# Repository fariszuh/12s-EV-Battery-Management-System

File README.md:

# 12s Battery Management System Research Project

## Introduction
*This repo used to collaborative work on BMS project*
This project initiated by Anargya Third Generation Electric Manager Plan, Abyqa on 2021.
He suggested us (4th Electric Generation) to create our independent BMS. 
In the next year, 2022, We (Rafli as Electric Manager, Faris as Head of Low Voltage Subdiv., Lazu as Head of High Voltage Subdiv) proposed new design according to last Molina BMS.
The schematics design is located in /Single Board 12s directory. Note: use the latest version _v<number>.sch

## My Last Progress
Last progress was programming with Arduino UNO (Faris, Gagas). 
The code located inside /Code directory.

## Challenge
PCB had been assembly with the components, but the SPI communication to LTC's register still couldn't be read. 
This problem probably caused by thin route layer between component pin to LTC. You can re-route Eagle board file and print again.
Suggestion: use thicker path and more than 2 layer.

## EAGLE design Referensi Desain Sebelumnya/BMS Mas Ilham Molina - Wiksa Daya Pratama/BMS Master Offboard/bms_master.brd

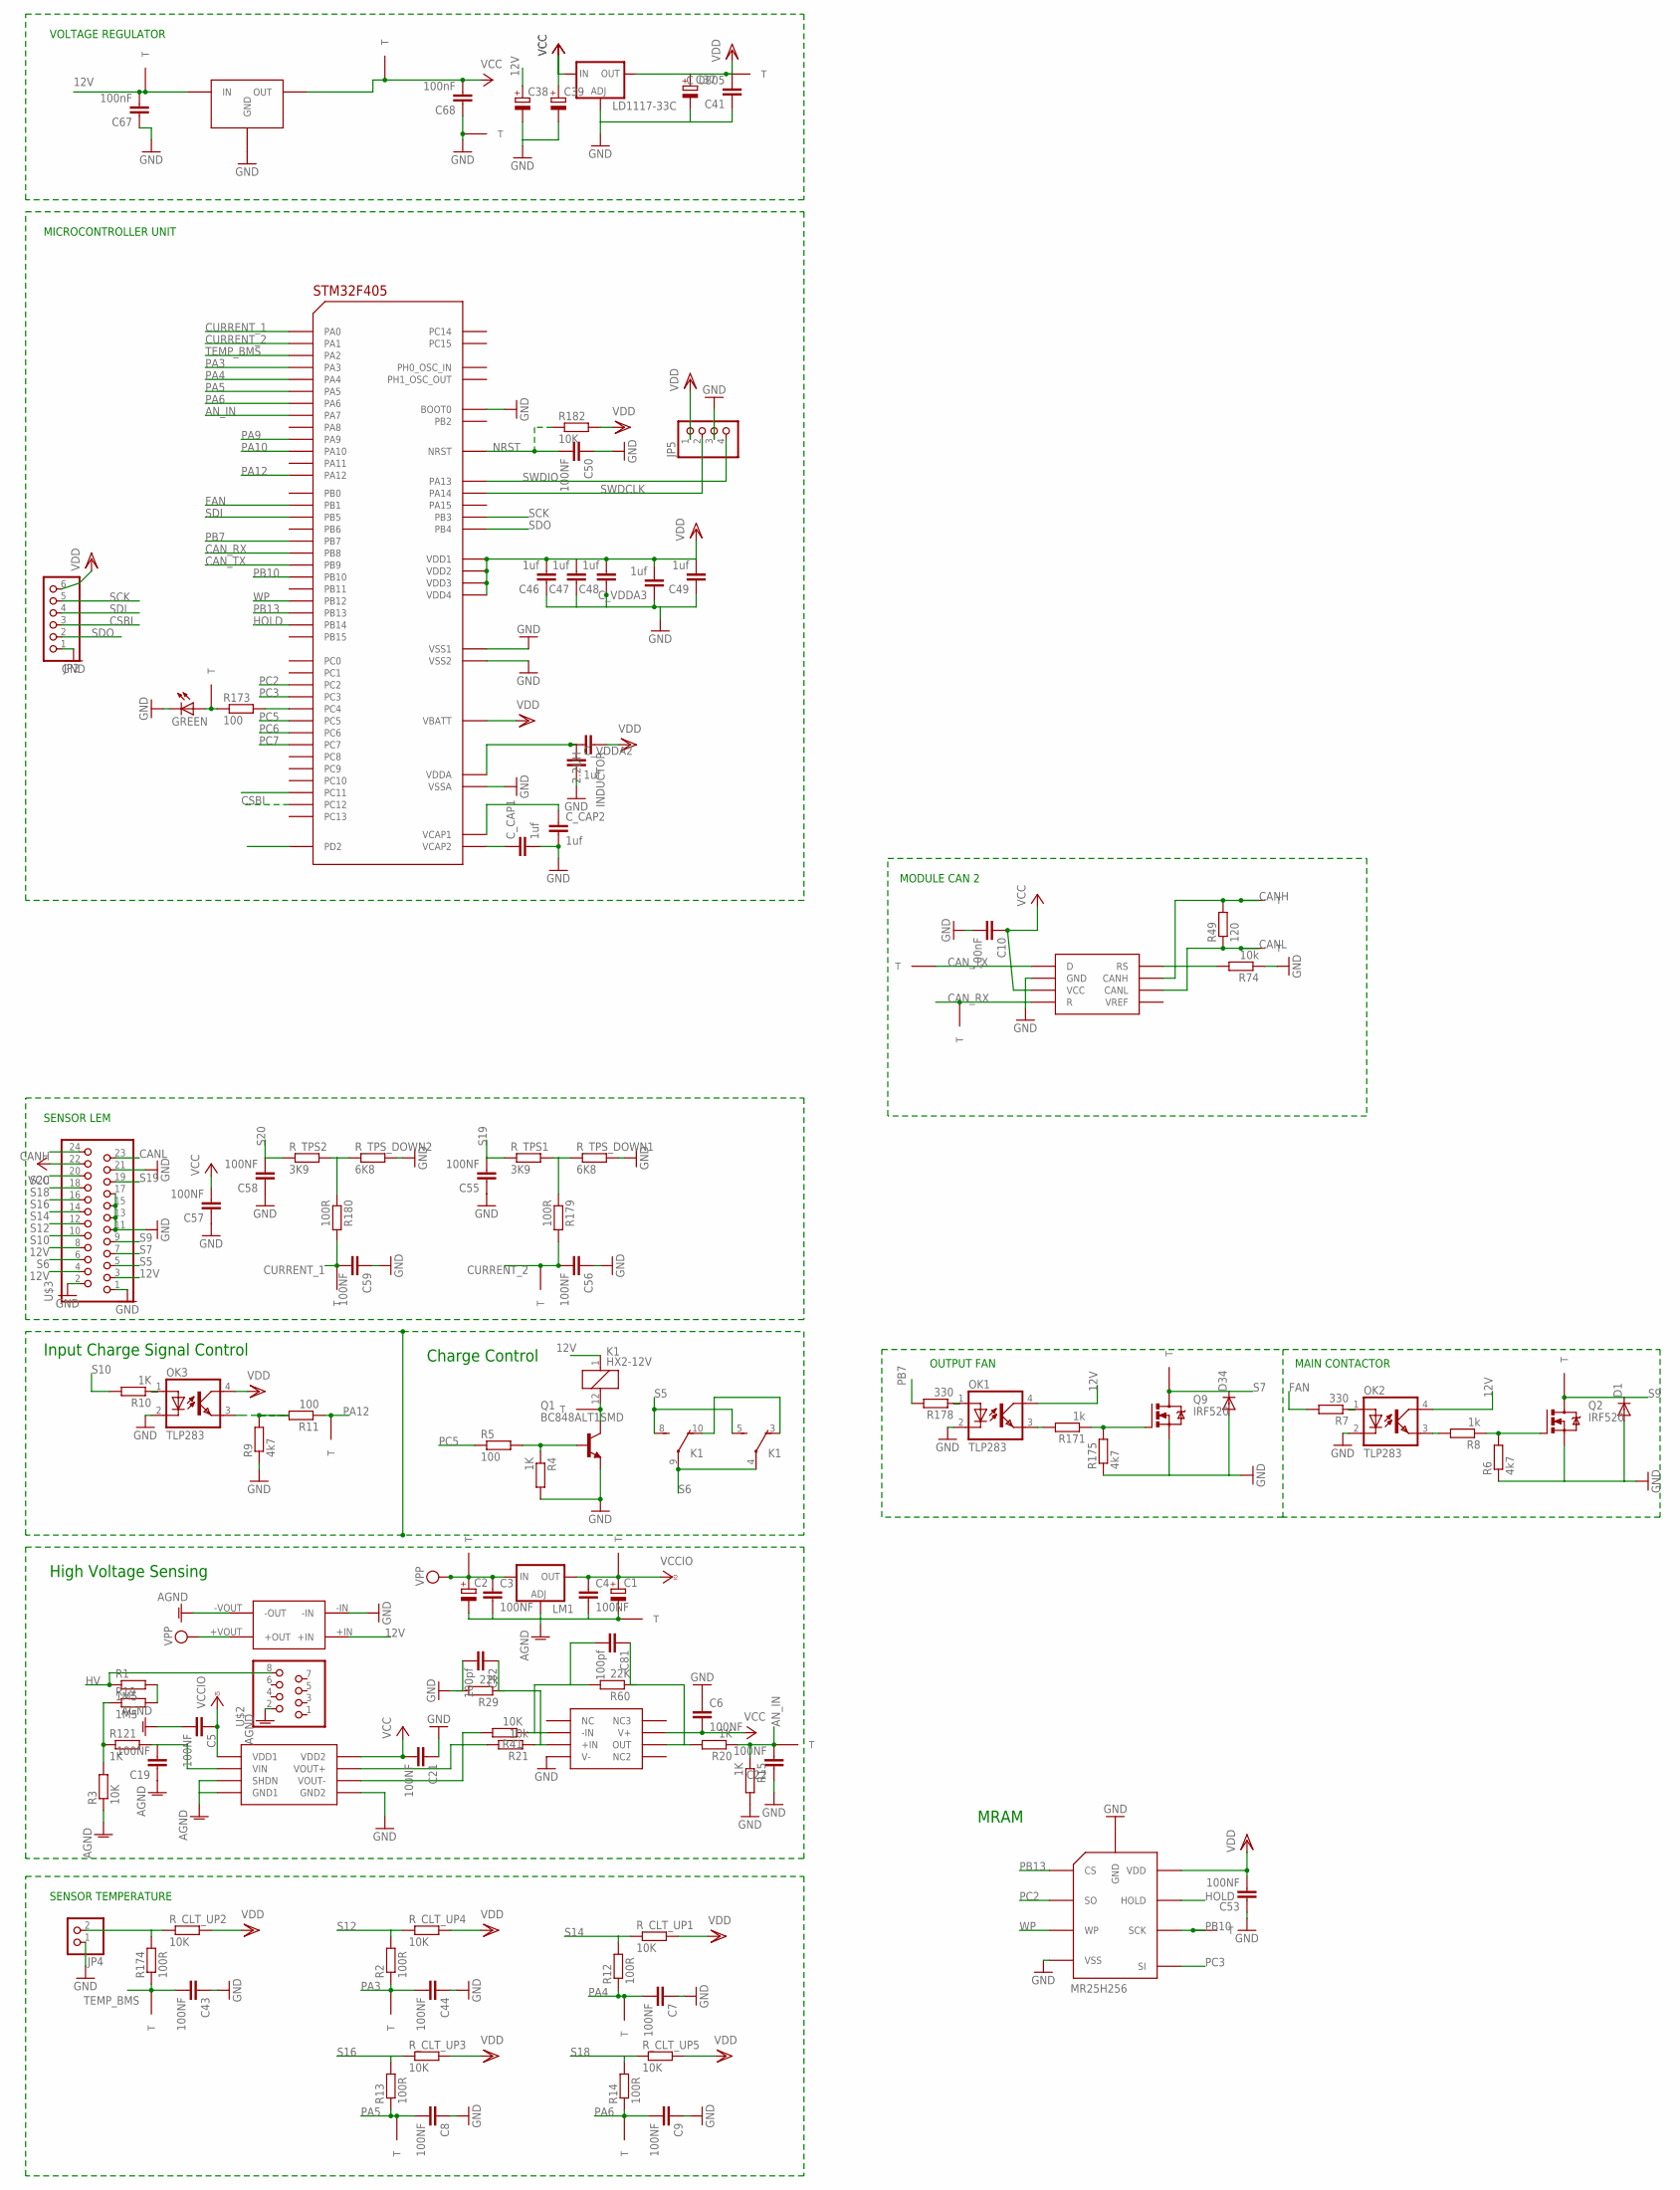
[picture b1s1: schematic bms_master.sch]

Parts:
C1, C37, C39: CPOL-EU153CLV-0605; 153CLV-0605
C2, C38: CPOL-EU153CLV-0810; 153CLV-0810
C3, C4, C5, C6, C7, C8, C9, C19, C21, C22, C43, C44, C50, C53, C55, C56, C57, C58, C59: 100NF; C_0805
C10, C67, C68: 100nF; C_0805
C41: C_0805
C46, C47, C48, C49: 1uf; C_0805
C81, C82: 100pf; C_0805
C_CAP1, C_CAP2: 1uf; C_0805
C_VDDA2, C_VDDA3: 1uf; C_0805
D1, D34: DIODE-SOD80C; SOD80C
GREEN: LED3MM
INDUCTOR: 2.2UH; C0805K
JP2: PINHD-1X6; 1X06
JP4: PINHD-1X2/90; 1X02/90
JP5: PINHD-1X4; 1X04
K1: HX2-12V; HX
LD1117-33C: LM317MABDT; DPACK@1
LM1: LM317MABDT; DPACK@1
OK1, OK2, OK3: TLP283; MINI-FLAT-4
Q1: BC848ALT1SMD; SOT23
Q2, Q9: IRF520; D-PAK_TO252AA
R1, R19: 1M5; R1210
R2, R12, R13, R14, R174, R179, R180: 100R; R_0805
R3: 10K; R1210
R4, R10, R15, R20: 1K; R_0805
R5, R11, R173: 100; R_0805
R6, R9, R175: 4k7; R_0805
R7, R178: 330; R_0805
R8, R171: 1k; R_0805
R21, R74: 10k; R_0805
R29: 22k; R_0805
R41, R182: 10K; R_0805
R49: 120; 0207/7
R60: 22K; R_0805
R121: 1K; R_1210
R_CLT_UP1, R_CLT_UP2, R_CLT_UP3, R_CLT_UP4, R_CLT_UP5: 10K; R_0805
R_TPS1, R_TPS2: 3K9; R_0805
R_TPS_DOWN1, R_TPS_DOWN2: 6K8; R_0805
U8: MCP2551; SN65HVD230
U$1: NWD5-12; NWD5
U$2: SOCKET8P; 8PIN
U$3: SOCKET24P; 24PIN
U$4, U$5, U$6, U$7, U$8, U$10, U$11, U$12, U$13, U$14, U$15, U$16, U$17, U$18, U$19, U$20, U$21, U$22, U$23, U$24, U$25, U$26, U$27, U$28, U$35: TESTPOINT
U$9: ACPL-C87B; STRETCHSO8
U$29: OKI-78SR-5; MDC_OKI
U$31: STM32F405; TQFP64
U$32: MR25H256; 8DFN
U$70: OPA237; SO-08

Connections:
12V: C38.+, C67.2, K1.1, OK1.4 (COL), OK2.4 (COL), U$1.+IN, U$3.3, U$3.4, U$3.8, U$5.P$1, U$29.1 (IN)
AGND: C1.-, C2.-, C3.2, C4.2, C5.2, C19.1, LM1.1 (ADJ), R3.1, U$1.-VOUT (-OUT), U$2.2, U$9.P$3 (SHDN), U$9.P$4 (GND1), U$20.P$1
AN_IN: C22.2, R15.1, R20.1, U$22.P$1, U$31.23 (PA7)
CANH: R49.2, U8.P$7 (CANH), U$3.24, U$12.P$1
CANL: R49.1, U8.P$6 (CANL), U$3.23, U$11.P$1
CAN_RX: U8.P$4 (R), U$8.P$1, U$31.61 (PB8)
CAN_TX: U8.P$1 (D), U$10.P$1, U$31.62 (PB9)
CSBI: JP2.3, U$31.53 (PC12)
CURRENT_1: C59.2, R180.2, U$14.P$1, U$31.14 (PA0)
CURRENT_2: C56.2, R179.2, U$13.P$1, U$31.15 (PA1)
FAN: R7.2, U$31.27 (PB1)
GND: C6.1, C7.1, C8.1, C9.1, C10.2, C21.1, C22.1, C37.-, C38.-, C39.-, C41.1, C43.1, C44.1, C46.1, C47.1, C48.1, C49.1, C50.1, C53.1, C55.1, C56.1, C57.1, C58.1, C59.1, C67.1, C68.1, C82.2, C_CAP1.2, C_CAP2.2, C_VDDA2.2, C_VDDA3.1, D1.A, D34.A, GREEN.K (C), JP2.1, JP4.1, JP5.3, LD1117-33C.1 (ADJ), OK1.2 (C), OK2.2 (C), OK3.2 (C), Q1.2 (E), Q2.1 (S), Q9.1 (S), R4.2, R6.1, R9.1, R15.2, R29.2, R74.1, R175.1, R_TPS_DOWN1.2, R_TPS_DOWN2.2, U8.P$2 (GND), U$1.-IN, U$3.1, U$3.2, U$3.11, U$3.13, U$3.15, U$3.17, U$3.21, U$4.P$1, U$9.P$5 (GND2), U$29.2 (GND), U$31.12 (VSSA), U$31.18 (VSS1), U$31.60 (BOOT0), U$31.63 (VSS2), U$32.P$4 (VSS), U$32.P$9 (GND), U$70.4 (V-)
HOLD: U$31.35 (PB14), U$32.P$7 (HOLD)
HV: R1.1, U$2.8
unnamed: Q2.3 (G), R6.2, R8.1
unnamed: K1.12 (2), Q1.3 (C), U$16.P$1
unnamed: OK2.1 (A), R7.1
unnamed: C19.2, R121.2, U$9.P$2 (VIN)
unnamed: OK2.3 (EMIT), R8.2
unnamed: R21.2, U$9.P$7 (VOUT+)
unnamed: Q1.1 (B), R4.1, R5.2
unnamed: K1.3 (O), K1.10 (O)
unnamed: C81.2, R41.1, R60.2, U$70.2 (-IN)
unnamed: R41.2, U$9.P$6 (VOUT-)
unnamed: OK3.1 (A), R10.1
unnamed: C82.1, R21.1, R29.1, U$70.3 (+IN)
unnamed: OK3.3 (EMIT), R9.2, R11.2
unnamed: R3.2, R19.1, R121.1
unnamed: R74.2, U8.P$8 (RS)
unnamed: R1.2, R19.2
unnamed: C_CAP1.1, U$31.47 (VCAP2)
unnamed: C_CAP2.1, U$31.31 (VCAP1)
unnamed: R173.2, U$31.24 (PC4)
unnamed: GREEN.A, R173.1, U$7.P$1
unnamed: JP4.2, R174.2, R_CLT_UP2.1
unnamed: R179.1, R_TPS1.2, R_TPS_DOWN1.1
unnamed: R180.1, R_TPS2.2, R_TPS_DOWN2.1
unnamed: Q9.3 (G), R171.1, R175.2
unnamed: OK1.1 (A), R178.1
unnamed: OK1.3 (EMIT), R171.2
unnamed: C_VDDA2.1, INDUCTOR.2, U$31.13 (VDDA)
NRST: C50.2, R182.1, U$31.7 (NRST)
PA3: C44.2, R2.1, U$24.P$1, U$31.17 (PA3)
PA4: C7.2, R12.1, U$27.P$1, U$31.20 (PA4)
PA5: C8.2, R13.1, U$25.P$1, U$31.21 (PA5)
PA6: C9.2, R14.1, U$26.P$1, U$31.22 (PA6)
PA9: U$31.42 (PA9)
PA10: U$31.43 (PA10)
PA12: R11.1, U$15.P$1, U$31.45 (PA12)
PB7: R178.2, U$31.59 (PB7)
PB10: U$28.P$1, U$31.29 (PB10), U$32.P$6 (SCK)
PB13: U$31.34 (PB13), U$32.P$1 (CS)
PC2: U$31.10 (PC2), U$32.P$2 (SO)
PC3: U$31.11 (PC3), U$32.P$5 (SI)
PC5: R5.1, U$31.25 (PC5)
PC6: U$31.37 (PC6)
PC7: U$31.38 (PC7)
S5: K1.5 (S), K1.8 (S), U$3.5
S6: K1.4, K1.9, U$3.6
S7: D34.C, Q9.4 (D), U$3.7, U$17.P$1
S9: D1.C, Q2.4 (D), U$3.9, U$18.P$1
S10: R10.2, U$3.10
S12: R2.2, R_CLT_UP4.1, U$3.12
S14: R12.2, R_CLT_UP1.1, U$3.14
S16: R13.2, R_CLT_UP3.1, U$3.16
S18: R14.2, R_CLT_UP5.1, U$3.18
S19: C55.2, R_TPS1.1, U$3.19
S20: C58.2, R_TPS2.1, U$3.20
SCK: JP2.5, U$31.55 (PB3)
SDI: JP2.4, U$31.57 (PB5)
SDO: JP2.2, U$31.56 (PB4)
SWDCLK: JP5.2, U$31.49 (PA14)
SWDIO: JP5.4, U$31.46 (PA13)
TEMP_BMS: C43.2, R174.1, U$23.P$1, U$31.16 (PA2)
VCC: C6.2, C10.1, C21.2, C39.+, C57.2, C68.2, LD1117-33C.3 (IN), U8.P$3 (VCC), U$3.22, U$9.P$8 (VDD2), U$29.3 (OUT), U$35.P$1, U$70.7 (V+)
VCCIO: C1.+, C4.1, C5.1, LM1.4 (OUT), U$9.P$1 (VDD1), U$19.P$1
VDD: C37.+, C41.2, C46.2, C47.2, C48.2, C49.2, C53.2, C_VDDA3.2, INDUCTOR.1, JP2.6, JP5.1, LD1117-33C.4 (OUT), OK3.4 (COL), R182.2, R_CLT_UP1.2, R_CLT_UP2.2, R_CLT_UP3.2, R_CLT_UP4.2, R_CLT_UP5.2, U$6.P$1, U$31.1 (VBATT), U$31.19 (VDD1), U$31.32 (VDD2), U$31.48 (VDD3), U$31.64 (VDD4), U$32.P$8 (VDD)
VPP: C2.+, C3.1, LM1.3 (IN), U$1.+VOUT (+OUT), U$21.P$1
WP: U$31.33 (PB12), U$32.P$3 (WP)
Y: C81.1, R20.2, R60.1, U$70.6 (OUT)

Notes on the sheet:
VOLTAGE REGULATOR
MICROCONTROLLER UNIT
SENSOR TEMPERATURE
SENSOR LEM
MRAM
High Voltage Sensing
Charge Control
OUTPUT FAN
MAIN CONTACTOR
Input Charge Signal Control
MODULE CAN 2

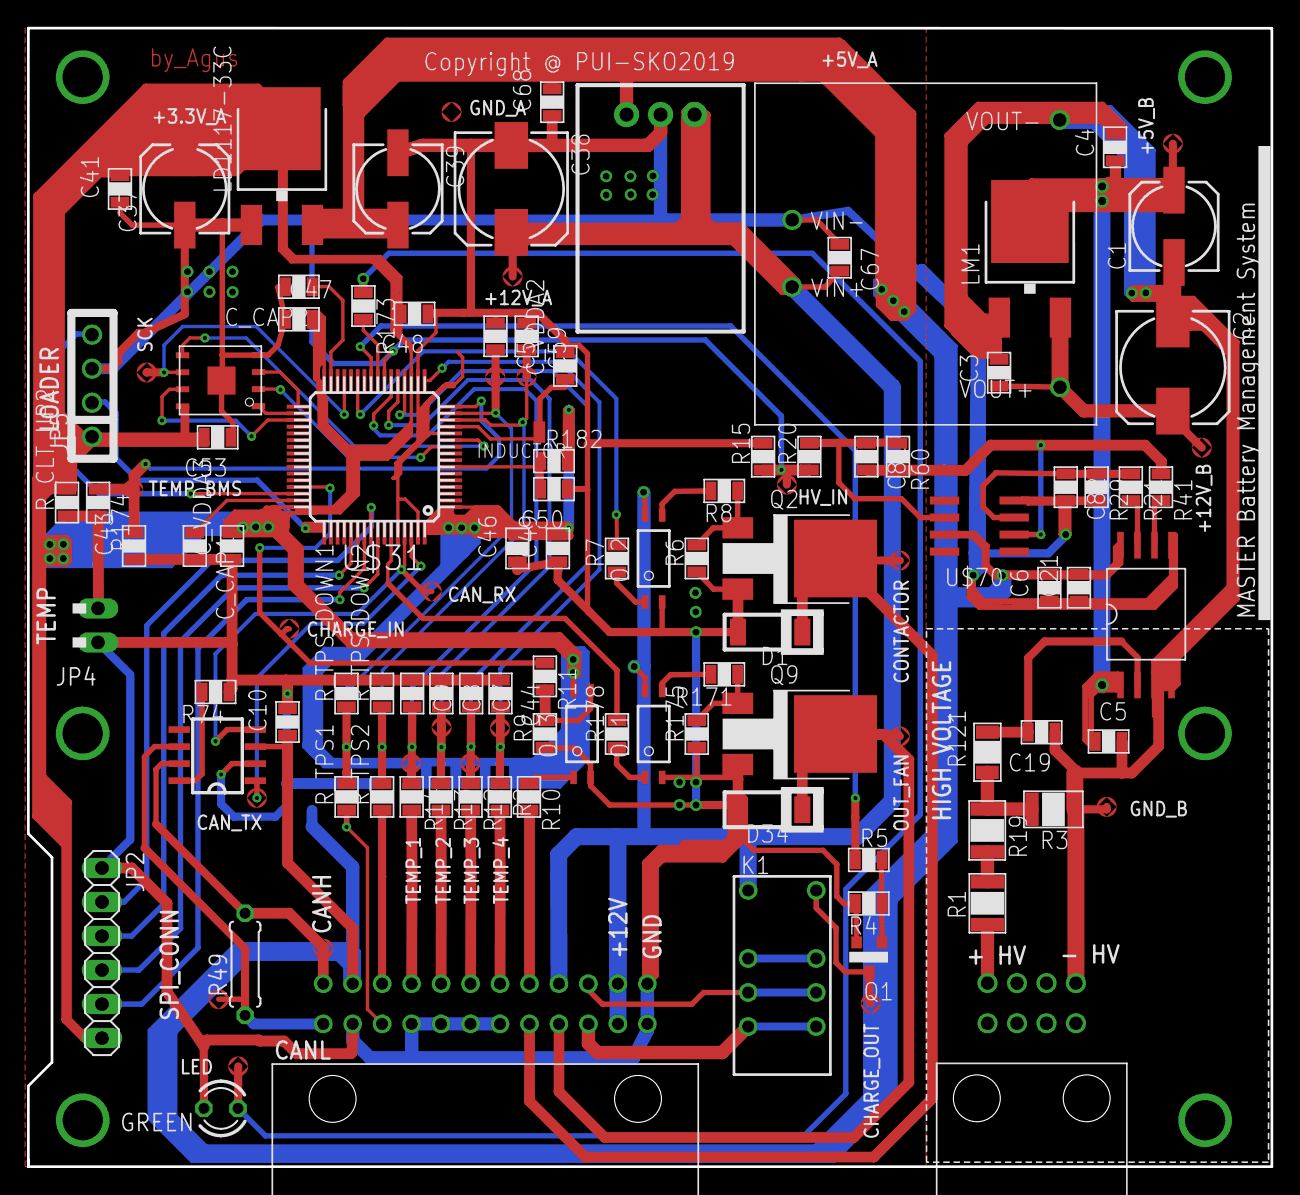
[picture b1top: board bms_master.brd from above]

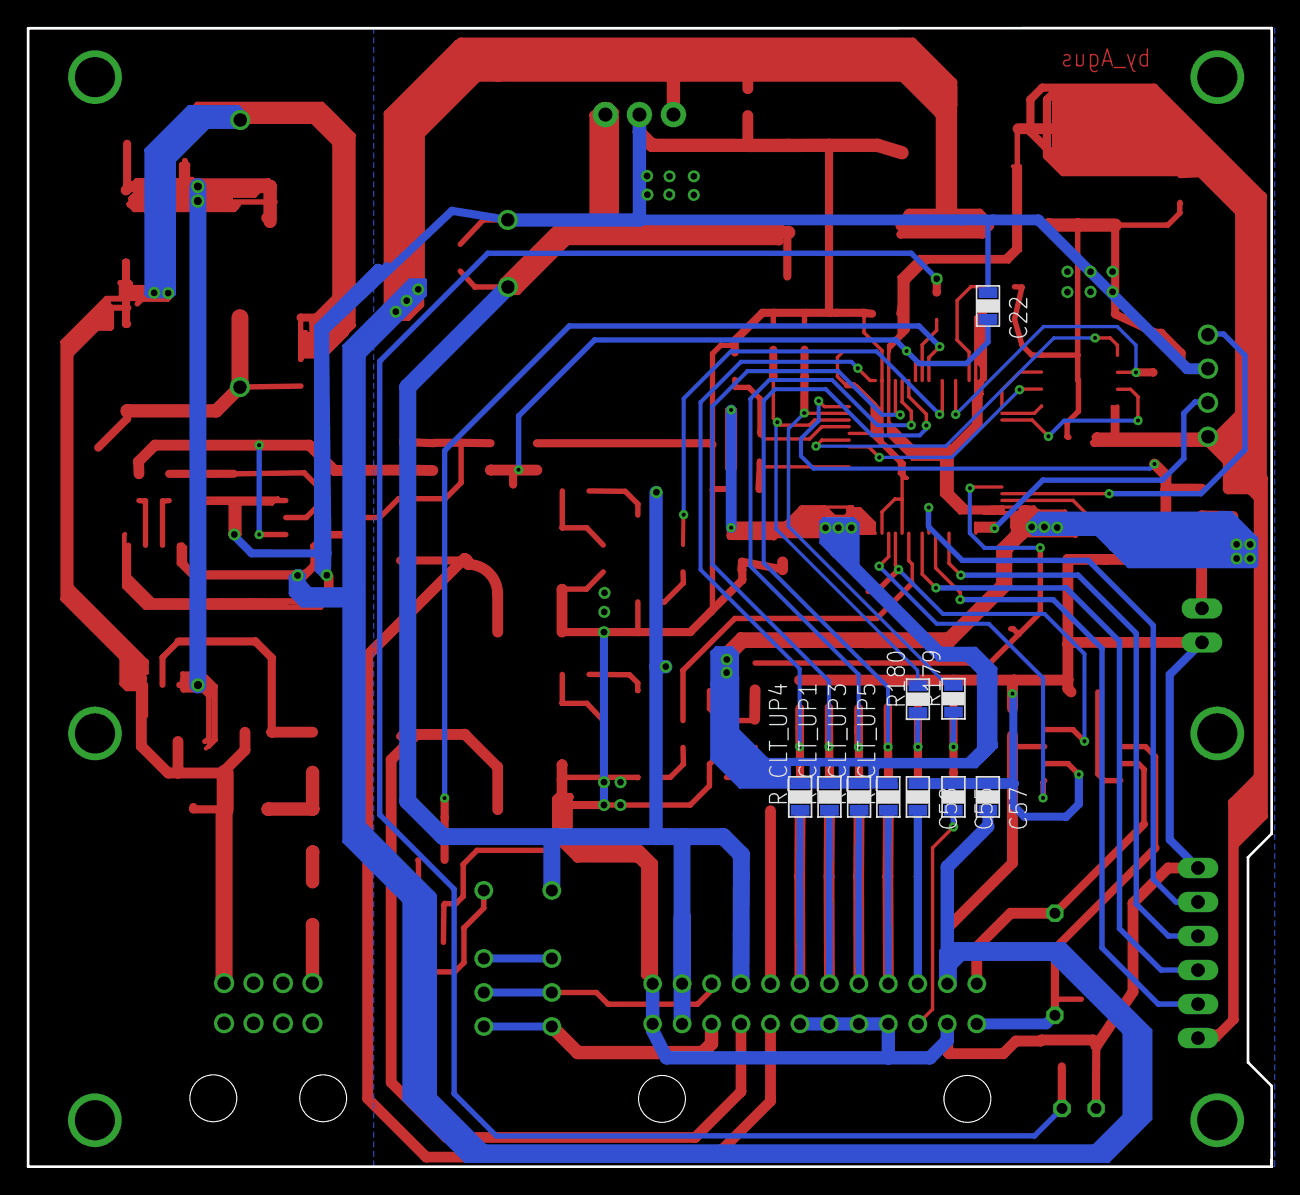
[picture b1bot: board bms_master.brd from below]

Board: 2 copper layers, 92.9 x 85.0 mm, 129 parts (10 on the bottom side), 76 nets.

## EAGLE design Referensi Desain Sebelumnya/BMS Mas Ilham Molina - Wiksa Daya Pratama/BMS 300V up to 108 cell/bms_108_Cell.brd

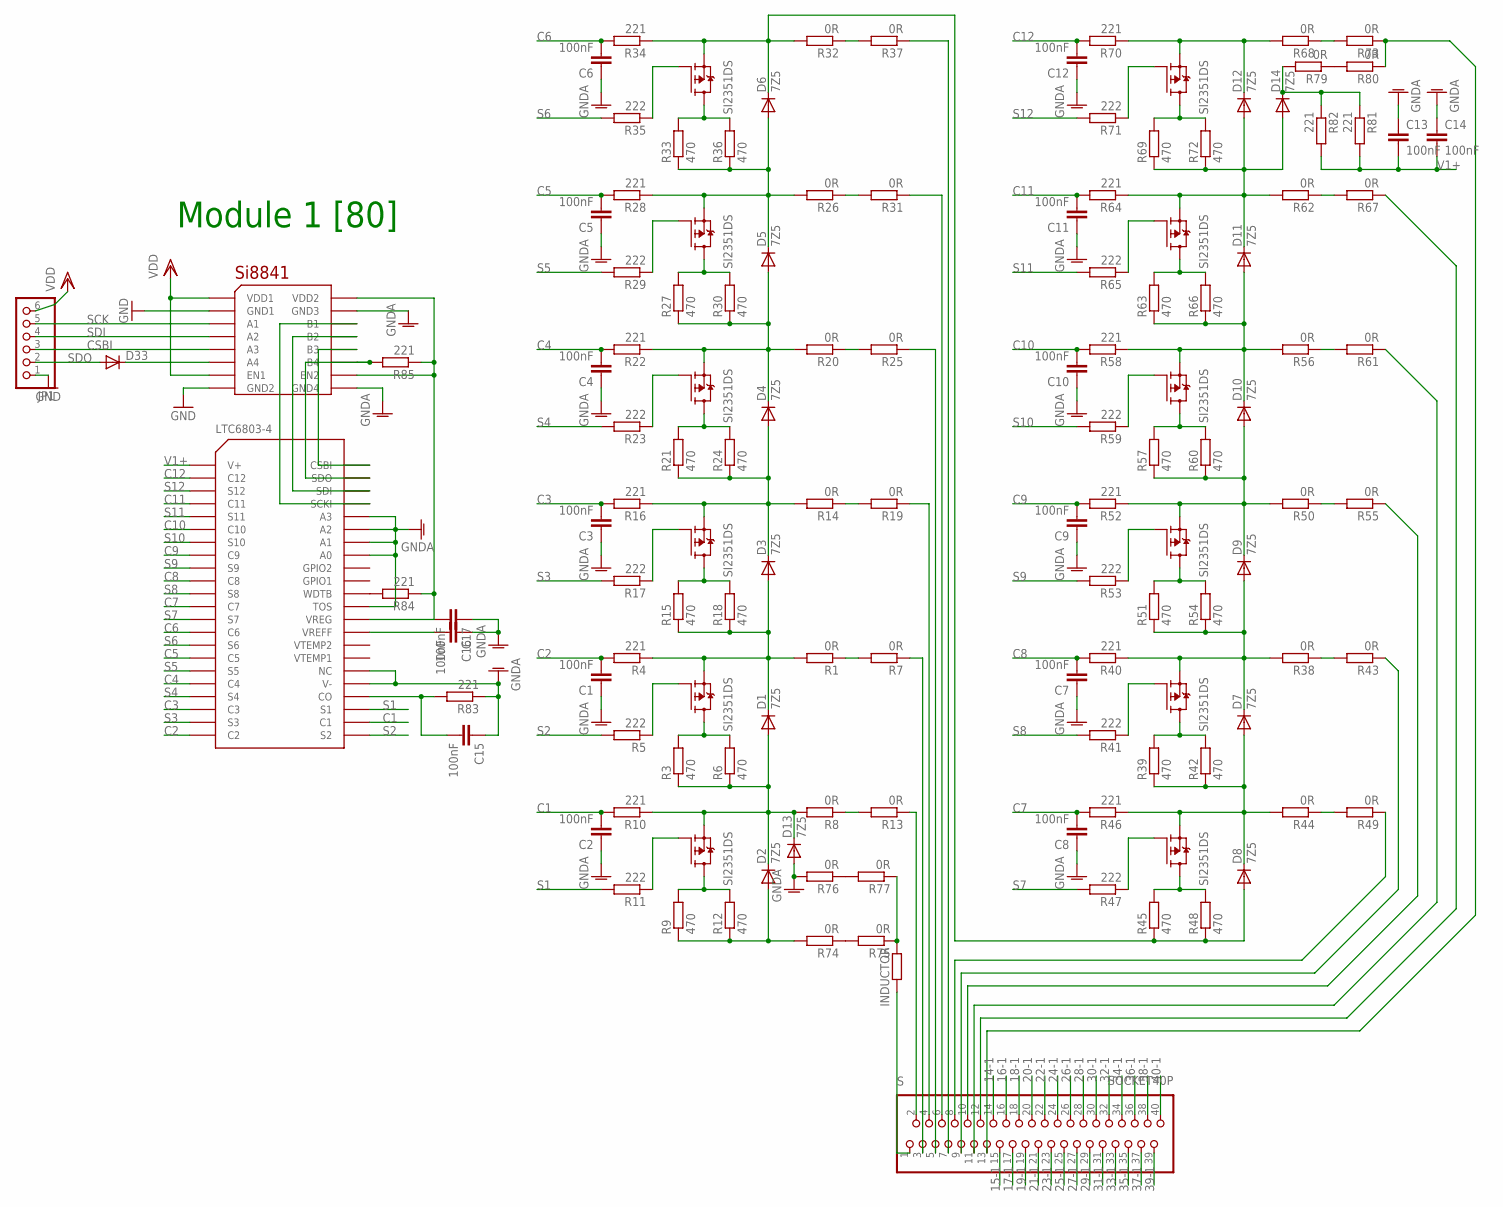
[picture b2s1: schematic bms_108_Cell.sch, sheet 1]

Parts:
C1, C2, C3, C4, C5, C6, C7, C8, C9, C10, C11, C12, C13, C14, C15, C16, C17: 100nF; C0805K
D1, D2, D3, D4, D5, D6, D7, D8, D9, D10, D11, D12, D13, D14: 7Z5; SMB
D33: DIODE-SOD123; SOD123
JP1: PINHD-1X6; 1X06
R1, R7, R8, R13, R14, R19, R20, R25, R26, R31, R32, R37, R38, R43, R44, R49, R50, R55, R56, R61, R62, R67, R68, R73, R74, R75, R76, R77, R79, R80: 0R; M1206
R3, R6, R9, R12, R15, R18, R21, R24, R27, R30, R33, R36, R39, R42, R45, R48, R51, R54, R57, R60, R63, R66, R69, R72: 470; R6332
R4, R10, R16, R22, R28, R34, R40, R46, R52, R58, R64, R70, R81, R82, R83, R84, R85: 221; R0805
R5, R11, R17, R23, R29, R35, R41, R47, R53, R59, R65, R71: 222; R0805
S: SOCKET40P; 40PIN
U$1: LTC6803-4; SSOP44
U$2: SI8841; SO16
U$3, U$4, U$5, U$6, U$7, U$8, U$9, U$10, U$11, U$12, U$13, U$14: SI2351DS; SOT23
U$15: INDUCTOR; L2012C

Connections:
14-1: S.14; also elsewhere on the board
15-1: S.15; also elsewhere on the board
16-1: S.16; also elsewhere on the board
17-1: S.17; also elsewhere on the board
18-1: S.18; also elsewhere on the board
19-1: S.19; also elsewhere on the board
20-1: S.20; also elsewhere on the board
21-1: S.21; also elsewhere on the board
22-1: S.22; also elsewhere on the board
23-1: S.23; also elsewhere on the board
24-1: S.24; also elsewhere on the board
25-1: S.25; also elsewhere on the board
26-1: S.26; also elsewhere on the board
27-1: S.27
28-1: S.28; also elsewhere on the board
29-1: S.29; also elsewhere on the board
30-1: S.30; also elsewhere on the board
31-1: S.31; also elsewhere on the board
32-1: S.32; also elsewhere on the board
33-1: S.33; also elsewhere on the board
34-1: S.34; also elsewhere on the board
35-1: S.35; also elsewhere on the board
36-1: S.36; also elsewhere on the board
37-1: S.37; also elsewhere on the board
38-1: S.38; also elsewhere on the board
39-1: S.39; also elsewhere on the board
40-1: S.40; also elsewhere on the board
C1: C2.2, R10.2, U$1.24 (C1)
C2: C1.2, R4.2, U$1.P$22 (C2)
C3: C3.2, R16.2, U$1.P$20 (C3)
C4: C4.2, R22.2, U$1.P$18 (C4)
C5: C5.2, R28.2, U$1.P$16 (C5)
C6: C6.2, R34.2, U$1.P$14 (C6)
C7: C8.2, R46.2, U$1.P$12 (C7)
C8: C7.2, R40.2, U$1.P$10 (C8)
C9: C9.2, R52.2, U$1.P$8 (C9)
C10: C10.2, R58.2, U$1.P$6 (C10)
C11: C11.2, R64.2, U$1.P$4 (C11)
C12: C12.2, R70.2, U$1.P$2 (C12)
CSBI: JP1.3, U$2.5 (A3); also elsewhere on the board
GND: JP1.1, U$2.2 (GND1), U$2.8 (GND2); also elsewhere on the board
GNDA: C1.1, C2.1, C3.1, C4.1, C5.1, C6.1, C7.1, C8.1, C9.1, C10.1, C11.1, C12.1, C13.1, C14.1, C15.1, C16.1, C17.1, D13.A, R76.2, R83.1, U$1.27 (V-), U$1.28 (NC), U$1.33 (TOS), U$1.37 (A0), U$1.38 (A1), U$1.39 (A2), U$1.40 (A3), U$2.9 (GND4), U$2.15 (GND3)
unnamed: R5.1, U$3.1 (G)
unnamed: R74.1, R75.2
unnamed: R3.2, R6.2, U$3.3 (D)
unnamed: D1.A, D2.C, D13.C, R3.1, R6.1, R8.2, R10.1, U$4.2 (S)
unnamed: R41.1, U$9.1 (G)
unnamed: R29.1, U$7.1 (G)
unnamed: R23.1, U$6.1 (G)
unnamed: R21.2, R24.2, U$6.3 (D)
unnamed: R1.1, R7.2
unnamed: R11.1, U$4.1 (G)
unnamed: R9.2, R12.2, U$4.3 (D)
unnamed: R76.1, R77.2
unnamed: D3.C, D4.A, R14.2, R16.1, R21.1, R24.1, U$5.2 (S)
unnamed: R8.1, R13.2
unnamed: R27.2, R30.2, U$7.3 (D)
unnamed: R17.1, U$5.1 (G)
unnamed: R15.2, R18.2, U$5.3 (D)
unnamed: D1.C, D3.A, R1.2, R4.1, R15.1, R18.1, U$3.2 (S)
unnamed: R20.1, R25.2
unnamed: R14.1, R19.2
unnamed: D4.C, D5.A, R20.2, R22.1, R27.1, R30.1, U$6.2 (S)
unnamed: R26.1, R31.2
unnamed: R75.1, R77.1, U$15.1
unnamed: R35.1, U$8.1 (G)
unnamed: R33.2, R36.2, U$8.3 (D)
unnamed: D5.C, D6.A, R26.2, R28.1, R33.1, R36.1, U$7.2 (S)
unnamed: R32.1, R37.2
unnamed: R39.2, R42.2, U$9.3 (D)
unnamed: D7.A, D8.C, R39.1, R42.1, R44.2, R46.1, U$10.2 (S)
unnamed: R38.1, R43.2
unnamed: R47.1, U$10.1 (G)
unnamed: R45.2, R48.2, U$10.3 (D)
unnamed: D6.C, D8.A, R32.2, R34.1, R45.1, R48.1, U$8.2 (S)
unnamed: R44.1, R49.2
unnamed: R53.1, U$11.1 (G)
unnamed: R51.2, R54.2, U$11.3 (D)
unnamed: D7.C, D9.A, R38.2, R40.1, R51.1, R54.1, U$9.2 (S)
unnamed: R50.1, R55.2
unnamed: D2.A, R9.1, R12.1, R74.2
unnamed: R59.1, U$12.1 (G)
unnamed: R57.2, R60.2, U$12.3 (D)
unnamed: D9.C, D10.A, R50.2, R52.1, R57.1, R60.1, U$11.2 (S)
unnamed: R56.1, R61.2
unnamed: R65.1, U$13.1 (G)
unnamed: R63.2, R66.2, U$13.3 (D)
unnamed: D10.C, D11.A, R56.2, R58.1, R63.1, R66.1, U$12.2 (S)
unnamed: R62.1, R67.2
unnamed: D12.C, R68.2, R70.1, U$14.2 (S)
unnamed: R71.1, U$14.1 (G)
unnamed: R69.2, R72.2, U$14.3 (D)
unnamed: D11.C, D12.A, D14.A, R62.2, R64.1, R69.1, R72.1, U$13.2 (S)
unnamed: R68.1, R73.2
unnamed: R85.2, U$1.43 (SDO), U$2.11 (B4)
unnamed: R79.1, R80.2
unnamed: C15.2, R83.2, U$1.26 (CO)
unnamed: D14.C, R79.2, R81.1, R82.1
unnamed: R73.1, R80.1, S.13
unnamed: C16.2, U$1.31 (VREFF)
unnamed: C17.2, R84.1, R85.1, U$1.32 (VREG), U$2.10 (EN2), U$2.16 (VDD2)
unnamed: U$1.41 (SCKI), U$2.14 (B1)
unnamed: R84.2, U$1.34 (WDTB)
unnamed: U$1.44 (CSBI), U$2.12 (B3)
unnamed: U$1.42 (SDI), U$2.13 (B2)
unnamed: S.1, U$15.2
unnamed: R13.1, S.2
unnamed: R7.1, S.3
unnamed: R19.1, S.4
unnamed: R25.1, S.5
unnamed: R31.1, S.6
unnamed: R37.1, S.7
unnamed: R49.1, S.8
unnamed: R43.1, S.9
unnamed: R55.1, S.10
unnamed: R61.1, S.11
unnamed: R67.1, S.12
unnamed: D33.C, U$2.6 (A4)
S1: R11.2, U$1.25 (S1)
S2: R5.2, U$1.23 (S2)
S3: R17.2, U$1.P$21 (S3)
S4: R23.2, U$1.P$19 (S4)
S5: R29.2, U$1.P$17 (S5)
S6: R35.2, U$1.P$15 (S6)
S7: R47.2, U$1.P$13 (S7)
S8: R41.2, U$1.P$11 (S8)
S9: R53.2, U$1.P$9 (S9)
S10: R59.2, U$1.P$7 (S10)
S11: R65.2, U$1.P$5 (S11)
S12: R71.2, U$1.P$3 (S12)
SCK: JP1.5, U$2.3 (A1); also elsewhere on the board
SDI: JP1.4, U$2.4 (A2); also elsewhere on the board
SDO: D33.A, JP1.2; also elsewhere on the board
V1+: C13.2, C14.2, R81.2, R82.2, U$1.P$1 (V+)
VDD: JP1.6, U$2.1 (VDD1), U$2.7 (EN1); also elsewhere on the board

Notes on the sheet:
Module 1 [80]

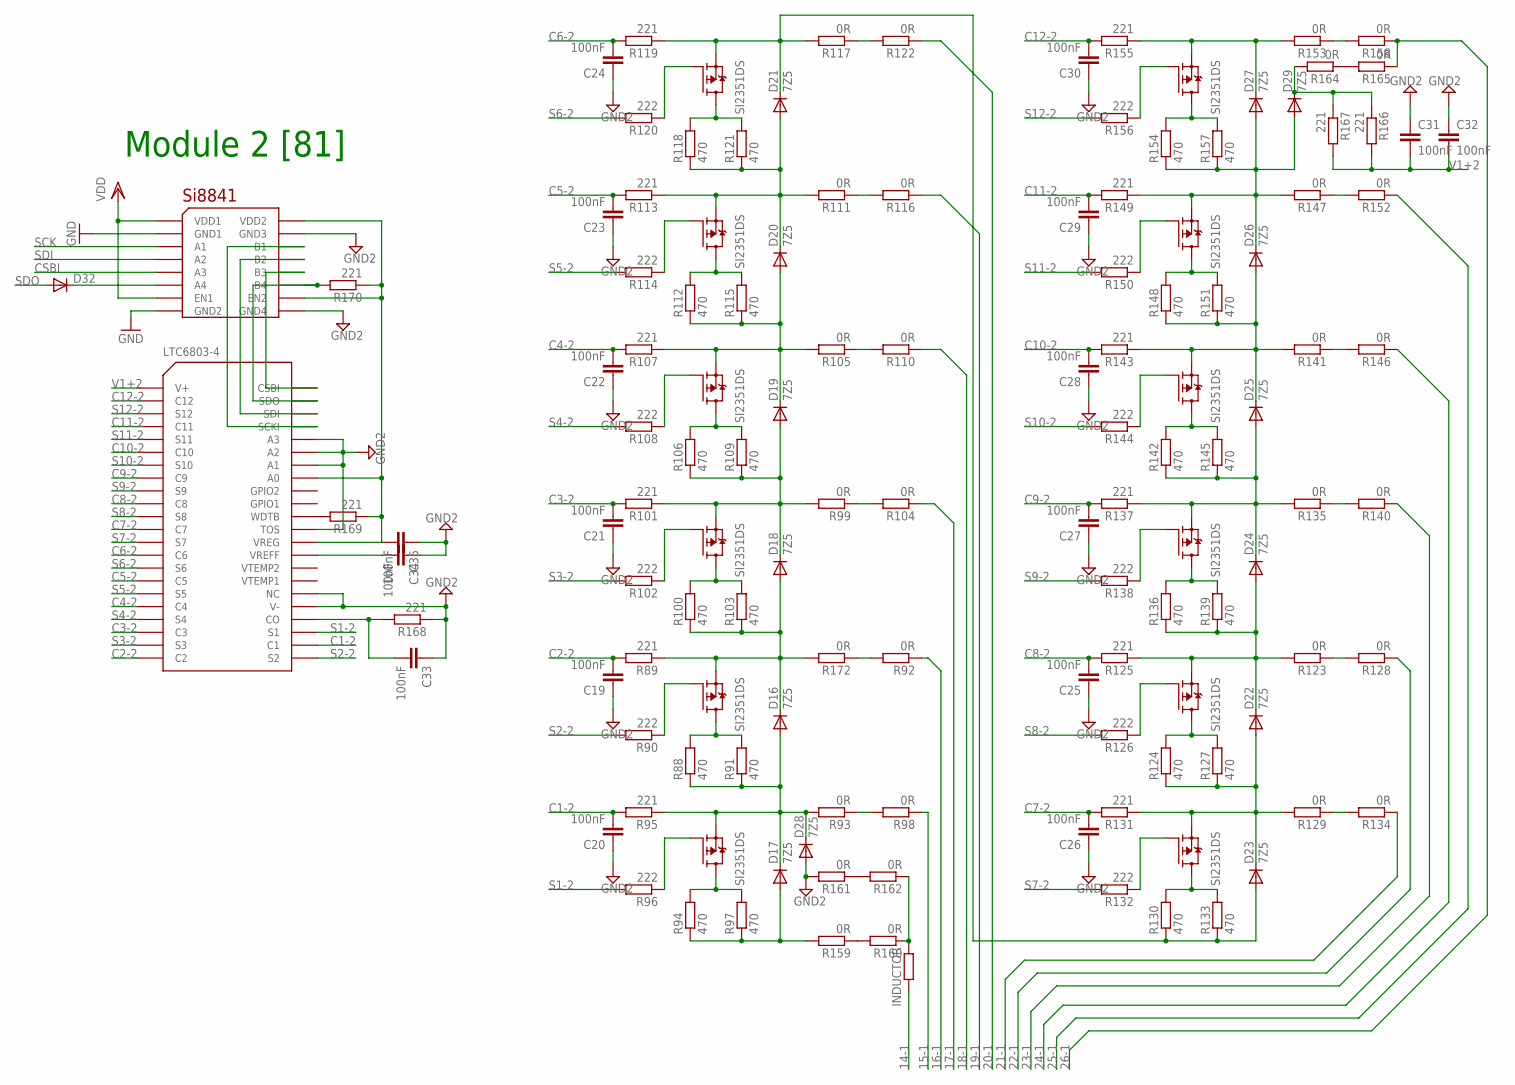
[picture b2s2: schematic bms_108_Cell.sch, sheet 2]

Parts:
C19, C20, C21, C22, C23, C24, C25, C26, C27, C28, C29, C30, C31, C32, C33, C34, C35: 100nF; C0805K
D16, D17, D18, D19, D20, D21, D22, D23, D24, D25, D26, D27, D28, D29: 7Z5; SMB
D32: DIODE-SOD123; SOD123
R88, R91, R94, R97, R100, R103, R106, R109, R112, R115, R118, R121, R124, R127, R130, R133, R136, R139, R142, R145, R148, R151, R154, R157: 470; R6332
R89, R95, R101, R107, R113, R119, R125, R131, R137, R143, R149, R155, R166, R167, R168, R169, R170: 221; R0805
R90, R96, R102, R108, R114, R120, R126, R132, R138, R144, R150, R156: 222; R0805
R92, R93, R98, R99, R104, R105, R110, R111, R116, R117, R122, R123, R128, R129, R134, R135, R140, R141, R146, R147, R152, R153, R158, R159, R160, R161, R162, R164, R165, R172: 0R; M1206
U$16: LTC6803-4; SSOP44
U$17: SI8841; SO16
U$18, U$19, U$20, U$21, U$22, U$23, U$24, U$25, U$26, U$27, U$28, U$29: SI2351DS; SOT23
U$30: INDUCTOR; L2012C

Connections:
14-1: U$30.2; also elsewhere on the board
15-1: R98.1; also elsewhere on the board
16-1: R92.1; also elsewhere on the board
17-1: R104.1; also elsewhere on the board
18-1: R110.1; also elsewhere on the board
19-1: R116.1; also elsewhere on the board
20-1: R122.1; also elsewhere on the board
21-1: R134.1; also elsewhere on the board
22-1: R128.1; also elsewhere on the board
23-1: R140.1; also elsewhere on the board
24-1: R146.1; also elsewhere on the board
25-1: R152.1; also elsewhere on the board
26-1: R158.1, R165.1; also elsewhere on the board
C1-2: C20.2, R95.2, U$16.24 (C1)
C2-2: C19.2, R89.2, U$16.P$22 (C2)
C3-2: C21.2, R101.2, U$16.P$20 (C3)
C4-2: C22.2, R107.2, U$16.P$18 (C4)
C5-2: C23.2, R113.2, U$16.P$16 (C5)
C6-2: C24.2, R119.2, U$16.P$14 (C6)
C7-2: C26.2, R131.2, U$16.P$12 (C7)
C8-2: C25.2, R125.2, U$16.P$10 (C8)
C9-2: C27.2, R137.2, U$16.P$8 (C9)
C10-2: C28.2, R143.2, U$16.P$6 (C10)
C11-2: C29.2, R149.2, U$16.P$4 (C11)
C12-2: C30.2, R155.2, U$16.P$2 (C12)
CSBI: U$17.5 (A3); also elsewhere on the board
GND: U$17.2 (GND1), U$17.8 (GND2); also elsewhere on the board
GND2: C19.1, C20.1, C21.1, C22.1, C23.1, C24.1, C25.1, C26.1, C27.1, C28.1, C29.1, C30.1, C31.1, C32.1, C33.1, C34.1, C35.1, D28.A, R161.2, R168.1, U$16.27 (V-), U$16.28 (NC), U$16.33 (TOS), U$16.38 (A1), U$16.39 (A2), U$16.40 (A3), U$17.9 (GND4), U$17.15 (GND3)
unnamed: R90.1, U$18.1 (G)
unnamed: R88.2, R91.2, U$18.3 (D)
unnamed: D16.A, D17.C, D28.C, R88.1, R91.1, R93.2, R95.1, U$19.2 (S)
unnamed: R92.2, R172.1
unnamed: R96.1, U$19.1 (G)
unnamed: R94.2, R97.2, U$19.3 (D)
unnamed: R93.1, R98.2
unnamed: R102.1, U$20.1 (G)
unnamed: R100.2, R103.2, U$20.3 (D)
unnamed: D16.C, D18.A, R89.1, R100.1, R103.1, R172.2, U$18.2 (S)
unnamed: R99.1, R104.2
unnamed: R108.1, U$21.1 (G)
unnamed: R106.2, R109.2, U$21.3 (D)
unnamed: D18.C, D19.A, R99.2, R101.1, R106.1, R109.1, U$20.2 (S)
unnamed: R105.1, R110.2
unnamed: R114.1, U$22.1 (G)
unnamed: R112.2, R115.2, U$22.3 (D)
unnamed: D19.C, D20.A, R105.2, R107.1, R112.1, R115.1, U$21.2 (S)
unnamed: R111.1, R116.2
unnamed: R120.1, U$23.1 (G)
unnamed: R118.2, R121.2, U$23.3 (D)
unnamed: D20.C, D21.A, R111.2, R113.1, R118.1, R121.1, U$22.2 (S)
unnamed: R117.1, R122.2
unnamed: R126.1, U$24.1 (G)
unnamed: R124.2, R127.2, U$24.3 (D)
unnamed: D22.A, D23.C, R124.1, R127.1, R129.2, R131.1, U$25.2 (S)
unnamed: R123.1, R128.2
unnamed: R132.1, U$25.1 (G)
unnamed: R130.2, R133.2, U$25.3 (D)
unnamed: D21.C, D23.A, R117.2, R119.1, R130.1, R133.1, U$23.2 (S)
unnamed: R129.1, R134.2
unnamed: R138.1, U$26.1 (G)
unnamed: R136.2, R139.2, U$26.3 (D)
unnamed: D22.C, D24.A, R123.2, R125.1, R136.1, R139.1, U$24.2 (S)
unnamed: R135.1, R140.2
unnamed: R144.1, U$27.1 (G)
unnamed: R142.2, R145.2, U$27.3 (D)
unnamed: D24.C, D25.A, R135.2, R137.1, R142.1, R145.1, U$26.2 (S)
unnamed: R141.1, R146.2
unnamed: R150.1, U$28.1 (G)
unnamed: R148.2, R151.2, U$28.3 (D)
unnamed: D25.C, D26.A, R141.2, R143.1, R148.1, R151.1, U$27.2 (S)
unnamed: R147.1, R152.2
unnamed: D27.C, R153.2, R155.1, U$29.2 (S)
unnamed: R156.1, U$29.1 (G)
unnamed: R154.2, R157.2, U$29.3 (D)
unnamed: D26.C, D27.A, D29.A, R147.2, R149.1, R154.1, R157.1, U$28.2 (S)
unnamed: R153.1, R158.2
unnamed: R159.1, R160.2
unnamed: R160.1, R162.1, U$30.1
unnamed: D17.A, R94.1, R97.1, R159.2
unnamed: R161.1, R162.2
unnamed: R164.1, R165.2
unnamed: D29.C, R164.2, R166.1, R167.1
unnamed: C33.2, R168.2, U$16.26 (CO)
unnamed: C34.2, U$16.31 (VREFF)
unnamed: C35.2, R169.1, R170.1, U$16.32 (VREG), U$16.37 (A0), U$17.10 (EN2), U$17.16 (VDD2)
unnamed: R169.2, U$16.34 (WDTB)
unnamed: R170.2, U$16.43 (SDO), U$17.11 (B4)
unnamed: U$16.44 (CSBI), U$17.12 (B3)
unnamed: U$16.42 (SDI), U$17.13 (B2)
unnamed: U$16.41 (SCKI), U$17.14 (B1)
unnamed: D32.C, U$17.6 (A4)
S1-2: R96.2, U$16.25 (S1)
S2-2: R90.2, U$16.23 (S2)
S3-2: R102.2, U$16.P$21 (S3)
S4-2: R108.2, U$16.P$19 (S4)
S5-2: R114.2, U$16.P$17 (S5)
S6-2: R120.2, U$16.P$15 (S6)
S7-2: R132.2, U$16.P$13 (S7)
S8-2: R126.2, U$16.P$11 (S8)
S9-2: R138.2, U$16.P$9 (S9)
S10-2: R144.2, U$16.P$7 (S10)
S11-2: R150.2, U$16.P$5 (S11)
S12-2: R156.2, U$16.P$3 (S12)
SCK: U$17.3 (A1); also elsewhere on the board
SDI: U$17.4 (A2); also elsewhere on the board
SDO: D32.A; also elsewhere on the board
V1+2: C31.2, C32.2, R166.2, R167.2, U$16.P$1 (V+)
VDD: U$17.1 (VDD1), U$17.7 (EN1); also elsewhere on the board

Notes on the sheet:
Module 2 [81]

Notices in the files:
Referensi Desain Sebelumnya/BMS Mas Ilham Molina - Wiksa Daya Pratama/BMS 300V up to 108 cell/bms_108_Cell.brd:
Copyright @ PUI-SKO 2019
parts and their libraries:
supply0: Copyright (C) 2007, Bob Starr
SparkFun-DiscreteSemi: Licensing: Creative Commons ShareAlike 4.0 International - https://creativecommons.org/licenses/by-sa/4.0
COPYRIGHT: Copyright (C) 2021 Ultra Librarian. All rights reserved.
